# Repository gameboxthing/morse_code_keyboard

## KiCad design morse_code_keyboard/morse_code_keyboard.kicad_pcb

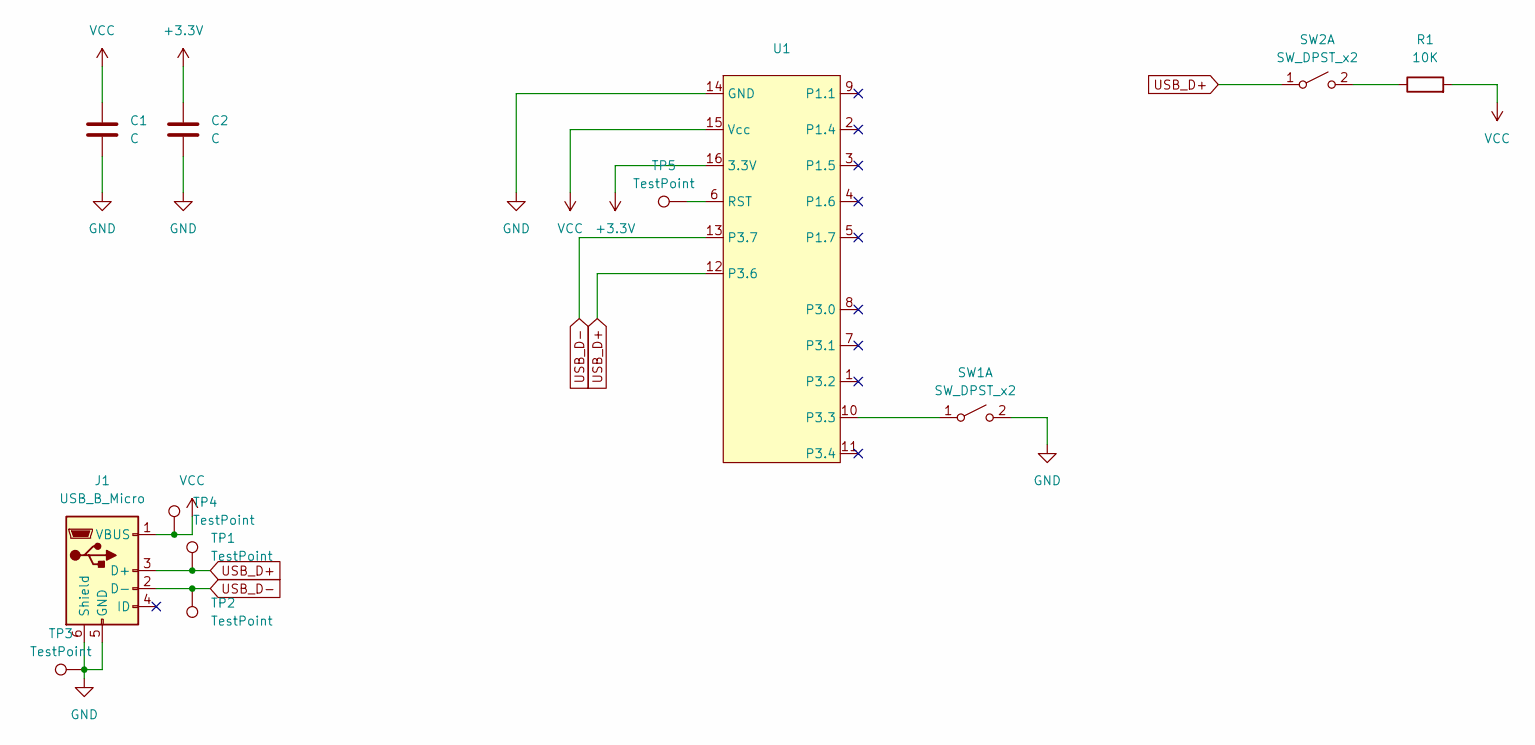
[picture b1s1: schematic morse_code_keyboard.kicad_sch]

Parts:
C1, C2: C; C_1206_3216Metric_Pad1.33x1.80mm_HandSolder
J1: USB_B_Micro; USB_Micro-B_Amphenol_10118193-0001LF_Horizontal
R1: 10K; R_1206_3216Metric_Pad1.30x1.75mm_HandSolder
SW1: SW_DPST_x2; SW_Cherry_MX_PCB_1.00u
SW2: SW_DPST_x2; TestPoint_2Pads_Pitch2.54mm_Drill0.8mm
TP1, TP2, TP3, TP4, TP5: TestPoint; TestPoint_Pad_D1.0mm
U1: SOP-16_3.9x9.9mm_P1.27mm

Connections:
+3.3V: C2.1, U1.16 (3.3V)
GND: C1.2, C2.2, J1.5 (GND), J1.6 (Shield), SW1.2 (B), TP3.1, U1.14 (GND)
unnamed: SW1.1 (A), U1.10 (P3.3)
unnamed: R1.1, SW2.2 (B)
unnamed: TP5.1, U1.6 (RST)
USB_D+: J1.3 (D+), SW2.1 (A), TP1.1, U1.12 (P3.6)
USB_D-: J1.2 (D-), TP2.1, U1.13 (P3.7)
VCC: C1.1, J1.1 (VBUS), R1.2, TP4.1, U1.15 (Vcc)

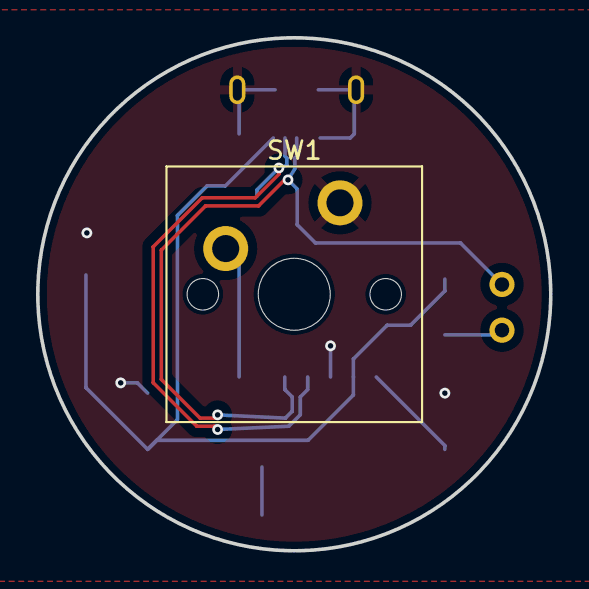
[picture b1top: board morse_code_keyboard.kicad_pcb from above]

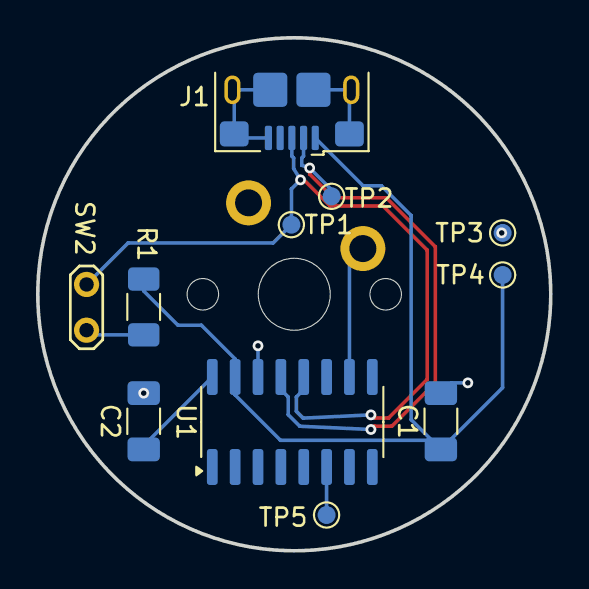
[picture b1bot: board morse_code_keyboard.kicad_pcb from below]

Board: 2 copper layers, 28.5 x 28.5 mm, 12 parts (11 on the bottom side), 8 nets.

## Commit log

2024-12-27 functional completion
